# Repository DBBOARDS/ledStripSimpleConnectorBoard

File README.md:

# ledStripSimpleConnectorBoard
These are the Eagle files for the LED Strip Simple Connector Board

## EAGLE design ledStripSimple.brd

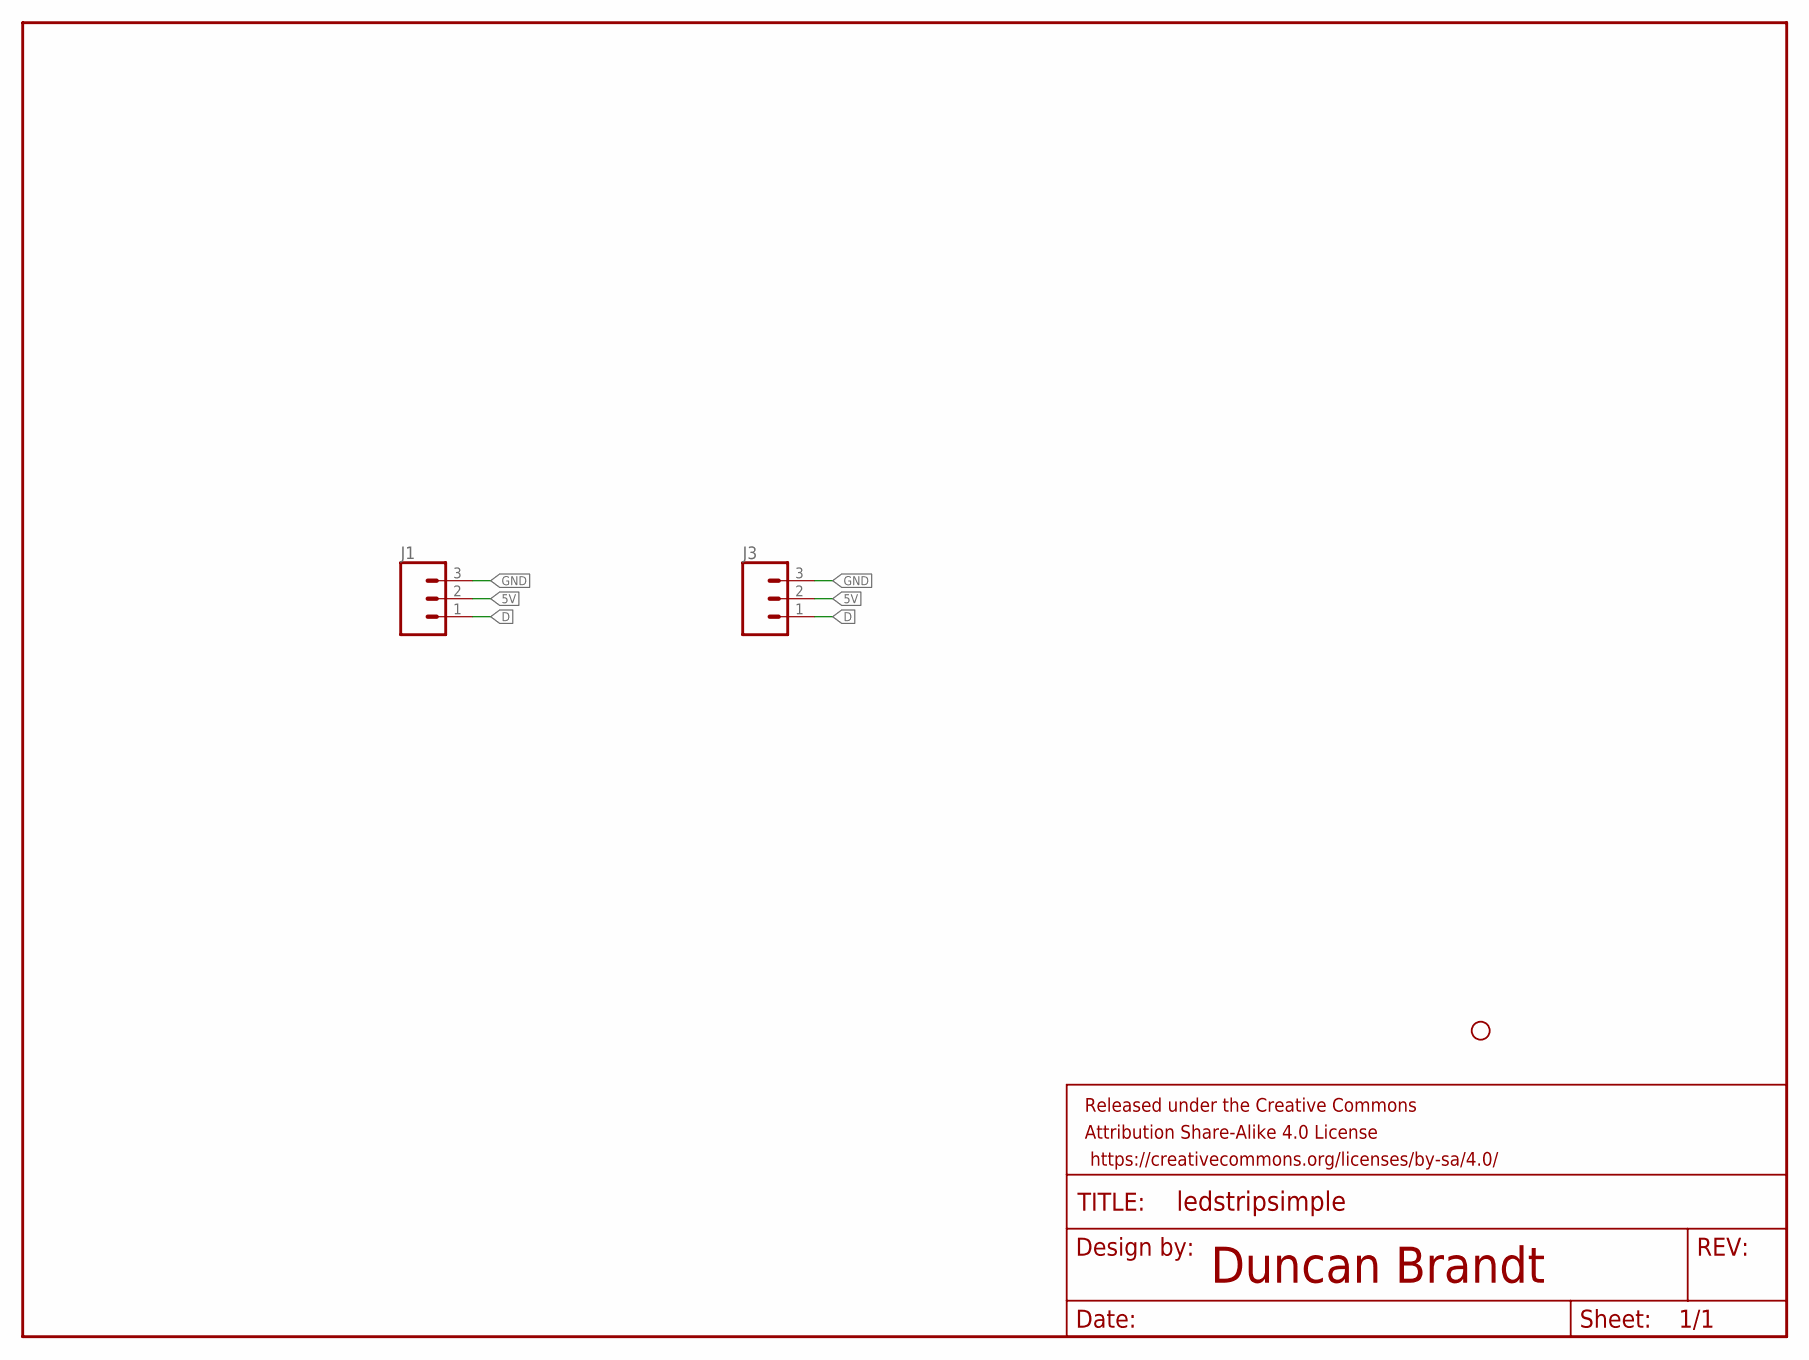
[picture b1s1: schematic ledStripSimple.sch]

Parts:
FRAME1: FRAME-LETTER; CREATIVE_COMMONS
H2: STAND-OFF
J1: CONN_03LONGPADS; 1X03_LEDSTRIP_LONGPADS
J3: CONN_03; 1X03

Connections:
5V: J1.2, J3.2
D: J1.1, J3.1
GND: J1.3, J3.3

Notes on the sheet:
Duncan Brandt

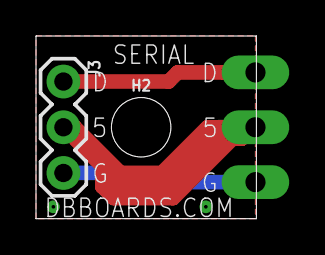
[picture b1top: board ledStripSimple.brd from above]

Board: 2 copper layers, 12.2 x 10.2 mm, 4 parts (1 on the bottom side), 3 nets.

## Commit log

2018-02-06 Board and Schematic Files for DB2005

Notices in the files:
parts and their libraries:
DB-SYMBOLS: Licensing: Creative Commons ShareAlike 4.0 International - https://creativecommons.org/licenses/by-sa/4.0
DB-SYMBOLS: Released under the Creative Commons Attribution Share-Alike 4.0 License
DB-SYMBOLS: https://creativecommons.org/licenses/by-sa/4.0
